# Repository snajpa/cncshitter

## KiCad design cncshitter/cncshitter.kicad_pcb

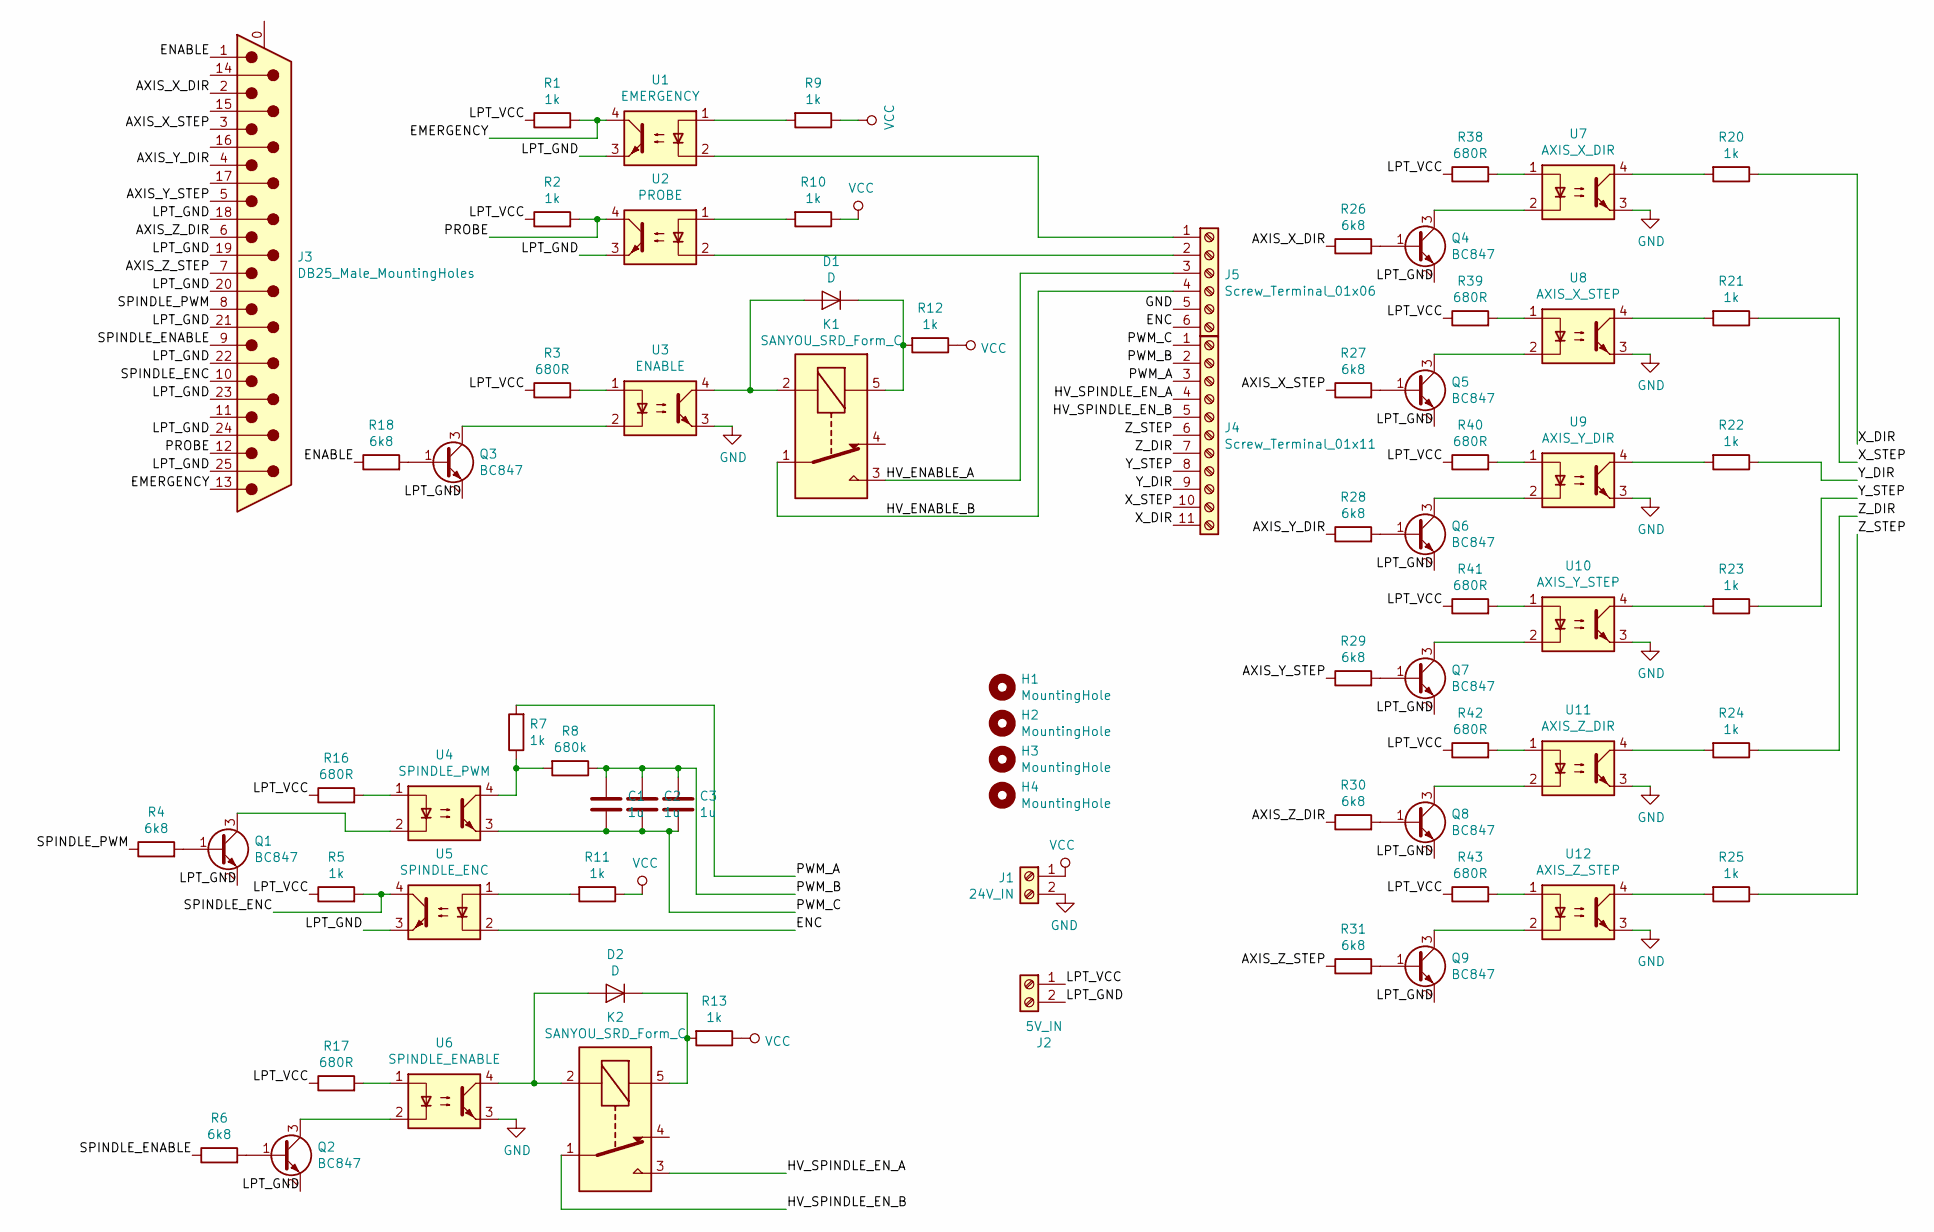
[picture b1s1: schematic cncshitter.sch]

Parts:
C1, C2, C3: 1u; C_1206_3216Metric_Pad1.42x1.75mm_HandSolder
D1, D2: D; D_DO-41_SOD81_P7.62mm_Horizontal
H1, H2, H3, H4: MountingHole; MountingHole_3mm_Pad
J1: 24V_IN; PhoenixContact_MCV_1,5_2-G-5.08_1x02_P5.08mm_Vertical
J2: 5V_IN; PhoenixContact_MCV_1,5_2-G-5.08_1x02_P5.08mm_Vertical
J3: DB25_Male_MountingHoles; DSUB-25_Male_Horizontal_P2.77x2.84mm_EdgePinOffset7.70mm_Ho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
J4: Screw_Terminal_01x11; PhoenixContact_MCV_1,5_11-G-5.08_1x11_P5.08mm_Vertical
J5: Screw_Terminal_01x06; PhoenixContact_MCV_1,5_6-G-5.08_1x06_P5.08mm_Vertical
K1, K2: SANYOU_SRD_Form_C; Relay_SPDT_SANYOU_SRD_Series_Form_C
Q1, Q2, Q3, Q4, Q5, Q6, Q7, Q8, Q9: BC847; SOT-23
R1, R2, R5, R7, R9, R10, R11, R12, R13, R20, R21, R22, R23, R24, R25: 1k; R_1206_3216Metric_Pad1.42x1.75mm_HandSolder
R3, R16, R17, R38, R39, R40, R41, R42, R43: 680R; R_1206_3216Metric_Pad1.42x1.75mm_HandSolder
R4, R6, R18, R26, R27, R28, R29, R30, R31: 6k8; R_1206_3216Metric_Pad1.42x1.75mm_HandSolder
R8: 680k; R_1206_3216Metric_Pad1.42x1.75mm_HandSolder
U1: EMERGENCY; SMDIP-4_W9.53mm
U2: PROBE; SMDIP-4_W9.53mm
U3: ENABLE; SMDIP-4_W9.53mm
U4: SPINDLE_PWM; SMDIP-4_W9.53mm
U5: SPINDLE_ENC; SMDIP-4_W9.53mm
U6: SPINDLE_ENABLE; SMDIP-4_W9.53mm
U7: AXIS_X_DIR; SMDIP-4_W9.53mm
U8: AXIS_X_STEP; SMDIP-4_W9.53mm
U9: AXIS_Y_DIR; SMDIP-4_W9.53mm
U10: AXIS_Y_STEP; SMDIP-4_W9.53mm
U11: AXIS_Z_DIR; SMDIP-4_W9.53mm
U12: AXIS_Z_STEP; SMDIP-4_W9.53mm

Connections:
/AXIS_X_DIR: J3.2, R26.1
/AXIS_X_STEP: J3.3, R27.1
/AXIS_Y_DIR: J3.4, R28.1
/AXIS_Y_STEP: J3.5, R29.1
/AXIS_Z_DIR: J3.6, R30.1
/AXIS_Z_STEP: J3.7, R31.1
/EMERGENCY: J3.13, R1.2, U1.4
/ENABLE: J3.1, R18.1
/ENC: J5.6, U5.2
/HV_ENABLE_A: J5.3, K1.3
/HV_ENABLE_B: J5.4, K1.1
/HV_SPINDLE_EN_A: J4.4, K2.3
/HV_SPINDLE_EN_B: J4.5, K2.1
/LPT_GND: J2.2, J3.18, J3.19, J3.20, J3.21, J3.22, J3.23, J3.24, J3.25, Q1.2 (E), Q2.2 (E), Q3.2 (E), Q4.2 (E), Q5.2 (E), Q6.2 (E), Q7.2 (E), Q8.2 (E), Q9.2 (E), U1.3, U2.3, U5.3
/LPT_VCC: J2.1, R1.1, R2.1, R3.1, R5.1, R16.1, R17.1, R38.1, R39.1, R40.1, R41.1, R42.1, R43.1; also elsewhere on the board
/PROBE: J3.12, R2.2, U2.4
/PWM_A: J4.3, R7.2
/PWM_B: C1.1, C2.1, C3.1, J4.2, R8.1
/PWM_C: C1.2, C2.2, C3.2, J4.1, U4.3
/SPINDLE_ENABLE: J3.9, R6.1
/SPINDLE_ENC: J3.10, R5.2, U5.4
/SPINDLE_PWM: J3.8, R4.1
/X_DIR: J4.11, R20.1
/X_STEP: J4.10, R21.1
/Y_DIR: J4.9, R22.1
/Y_STEP: J4.8, R23.1
/Z_DIR: J4.7, R24.1
/Z_STEP: J4.6, R25.1
GND: J1.2, J5.5, U3.3, U6.3, U7.3, U8.3, U9.3, U10.3, U11.3, U12.3
unnamed: D1.1 (K), K1.5, R12.2
unnamed: D1.2 (A), K1.2, U3.4
unnamed: D2.1 (K), K2.5, R13.2
unnamed: D2.2 (A), K2.2, U6.4
unnamed: J5.1, U1.2
unnamed: J5.2, U2.2
unnamed: Q1.1 (B), R4.2
unnamed 44: Q1.3 (C), U4.2; also elsewhere on the board
unnamed: Q2.1 (B), R6.2
unnamed 46: Q2.3 (C), U6.2; also elsewhere on the board
unnamed: Q3.1 (B), R18.2
unnamed 48: Q3.3 (C), U3.2; also elsewhere on the board
unnamed: Q4.1 (B), R26.2
unnamed 50: Q4.3 (C), U7.2; also elsewhere on the board
unnamed: Q5.1 (B), R27.2
unnamed 52: Q5.3 (C), U8.2; also elsewhere on the board
unnamed: Q6.1 (B), R28.2
unnamed 54: Q6.3 (C), U9.2; also elsewhere on the board
unnamed: Q7.1 (B), R29.2
unnamed 56: Q7.3 (C), U10.2; also elsewhere on the board
unnamed: Q8.1 (B), R30.2
unnamed 58: Q8.3 (C), U11.2; also elsewhere on the board
unnamed: Q9.1 (B), R31.2
unnamed 60: Q9.3 (C), U12.2; also elsewhere on the board
unnamed: R3.2, U3.1
unnamed: R7.1, R8.2, U4.4
unnamed: R9.2, U1.1
unnamed: R10.2, U2.1
unnamed: R11.2, U5.1
unnamed: R16.2, U4.1
unnamed: R17.2, U6.1
unnamed: R20.2, U7.4
unnamed: R21.2, U8.4
unnamed: R22.2, U9.4
unnamed: R23.2, U10.4
unnamed: R24.2, U11.4
unnamed: R25.2, U12.4
unnamed: R38.2, U7.1
unnamed: R39.2, U8.1
unnamed: R40.2, U9.1
unnamed: R41.2, U10.1
unnamed: R42.2, U11.1
unnamed: R43.2, U12.1
VCC: J1.1, R9.1, R10.1, R11.1, R12.1, R13.1

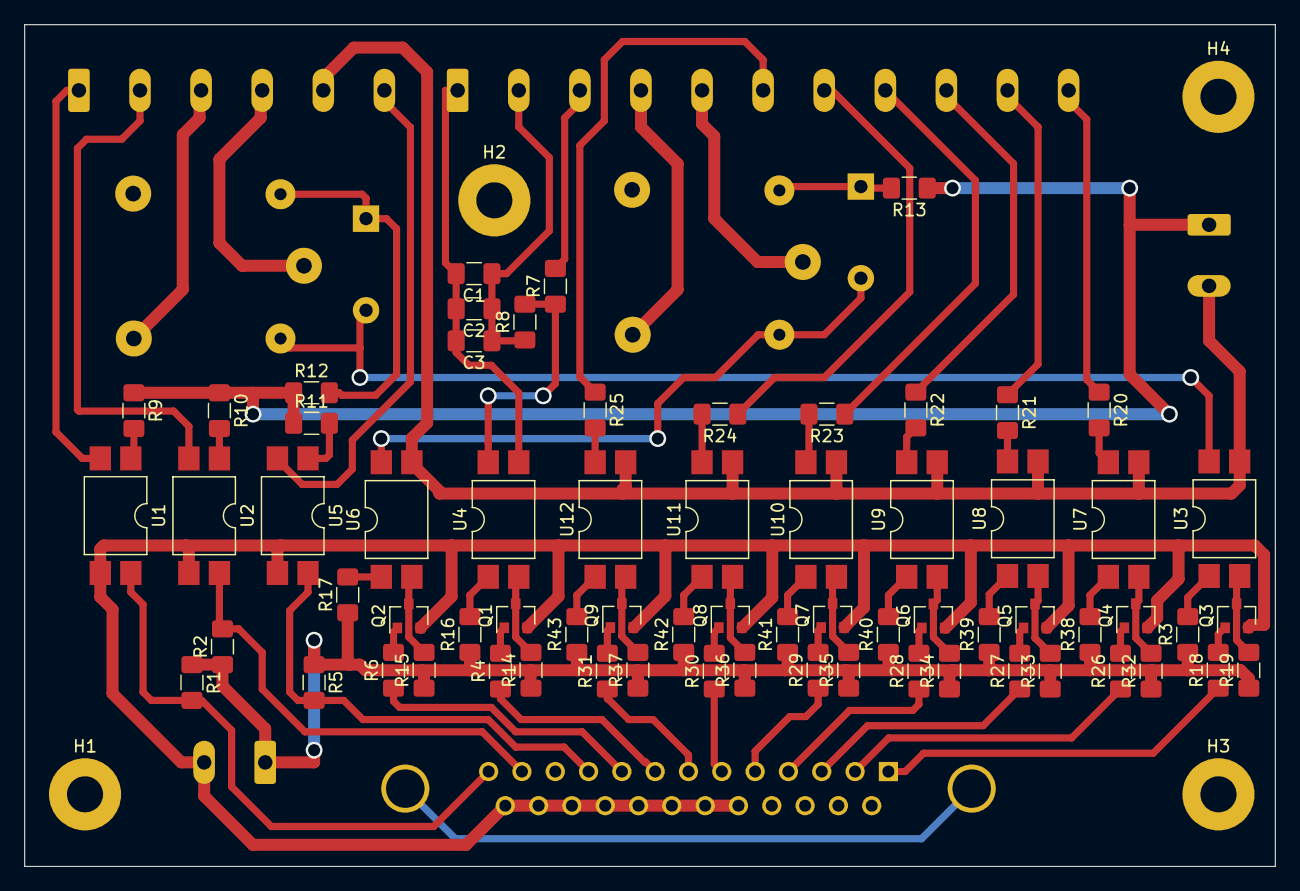
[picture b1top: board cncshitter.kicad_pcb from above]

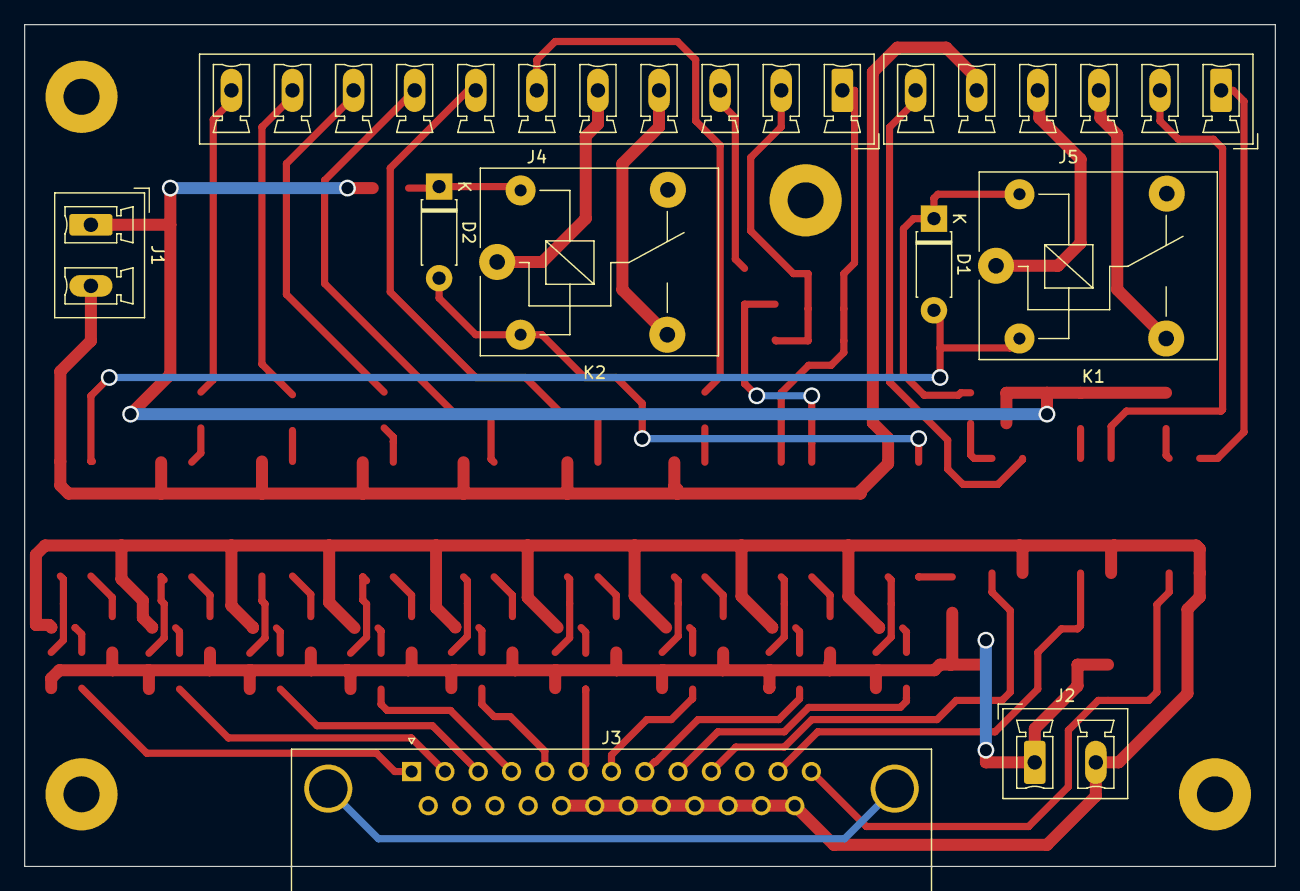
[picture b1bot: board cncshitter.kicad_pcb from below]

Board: 2 copper layers, 104.0 x 70.0 mm, 80 parts (9 on the bottom side), 73 nets.

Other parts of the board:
R14, R15, R19, R32, R33, R34, R35, R36, R37: 680R; R_1206_3216Metric_Pad1.42x1.75mm_HandSolder

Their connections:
/LPT_VCC: R14.1, R15.1, R19.1, R32.1, R33.1, R34.1, R35.1, R36.1, R37.1; also elsewhere on the board
unnamed 44: R14.2; also elsewhere on the board
unnamed 46: R15.2; also elsewhere on the board
unnamed 48: R19.2; also elsewhere on the board
unnamed 50: R32.2; also elsewhere on the board
unnamed 52: R33.2; also elsewhere on the board
unnamed 54: R34.2; also elsewhere on the board
unnamed 56: R35.2; also elsewhere on the board
unnamed 58: R36.2; also elsewhere on the board
unnamed 60: R37.2; also elsewhere on the board

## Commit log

2020-01-11 files
2020-01-11 v2 fixes
2020-01-11 v2 fixes 2
2020-01-11 v2 drc pass
2020-01-11 v3 smaller
2020-01-11 v3 fixed
2020-01-13 vkkt
2020-01-14 add svg
